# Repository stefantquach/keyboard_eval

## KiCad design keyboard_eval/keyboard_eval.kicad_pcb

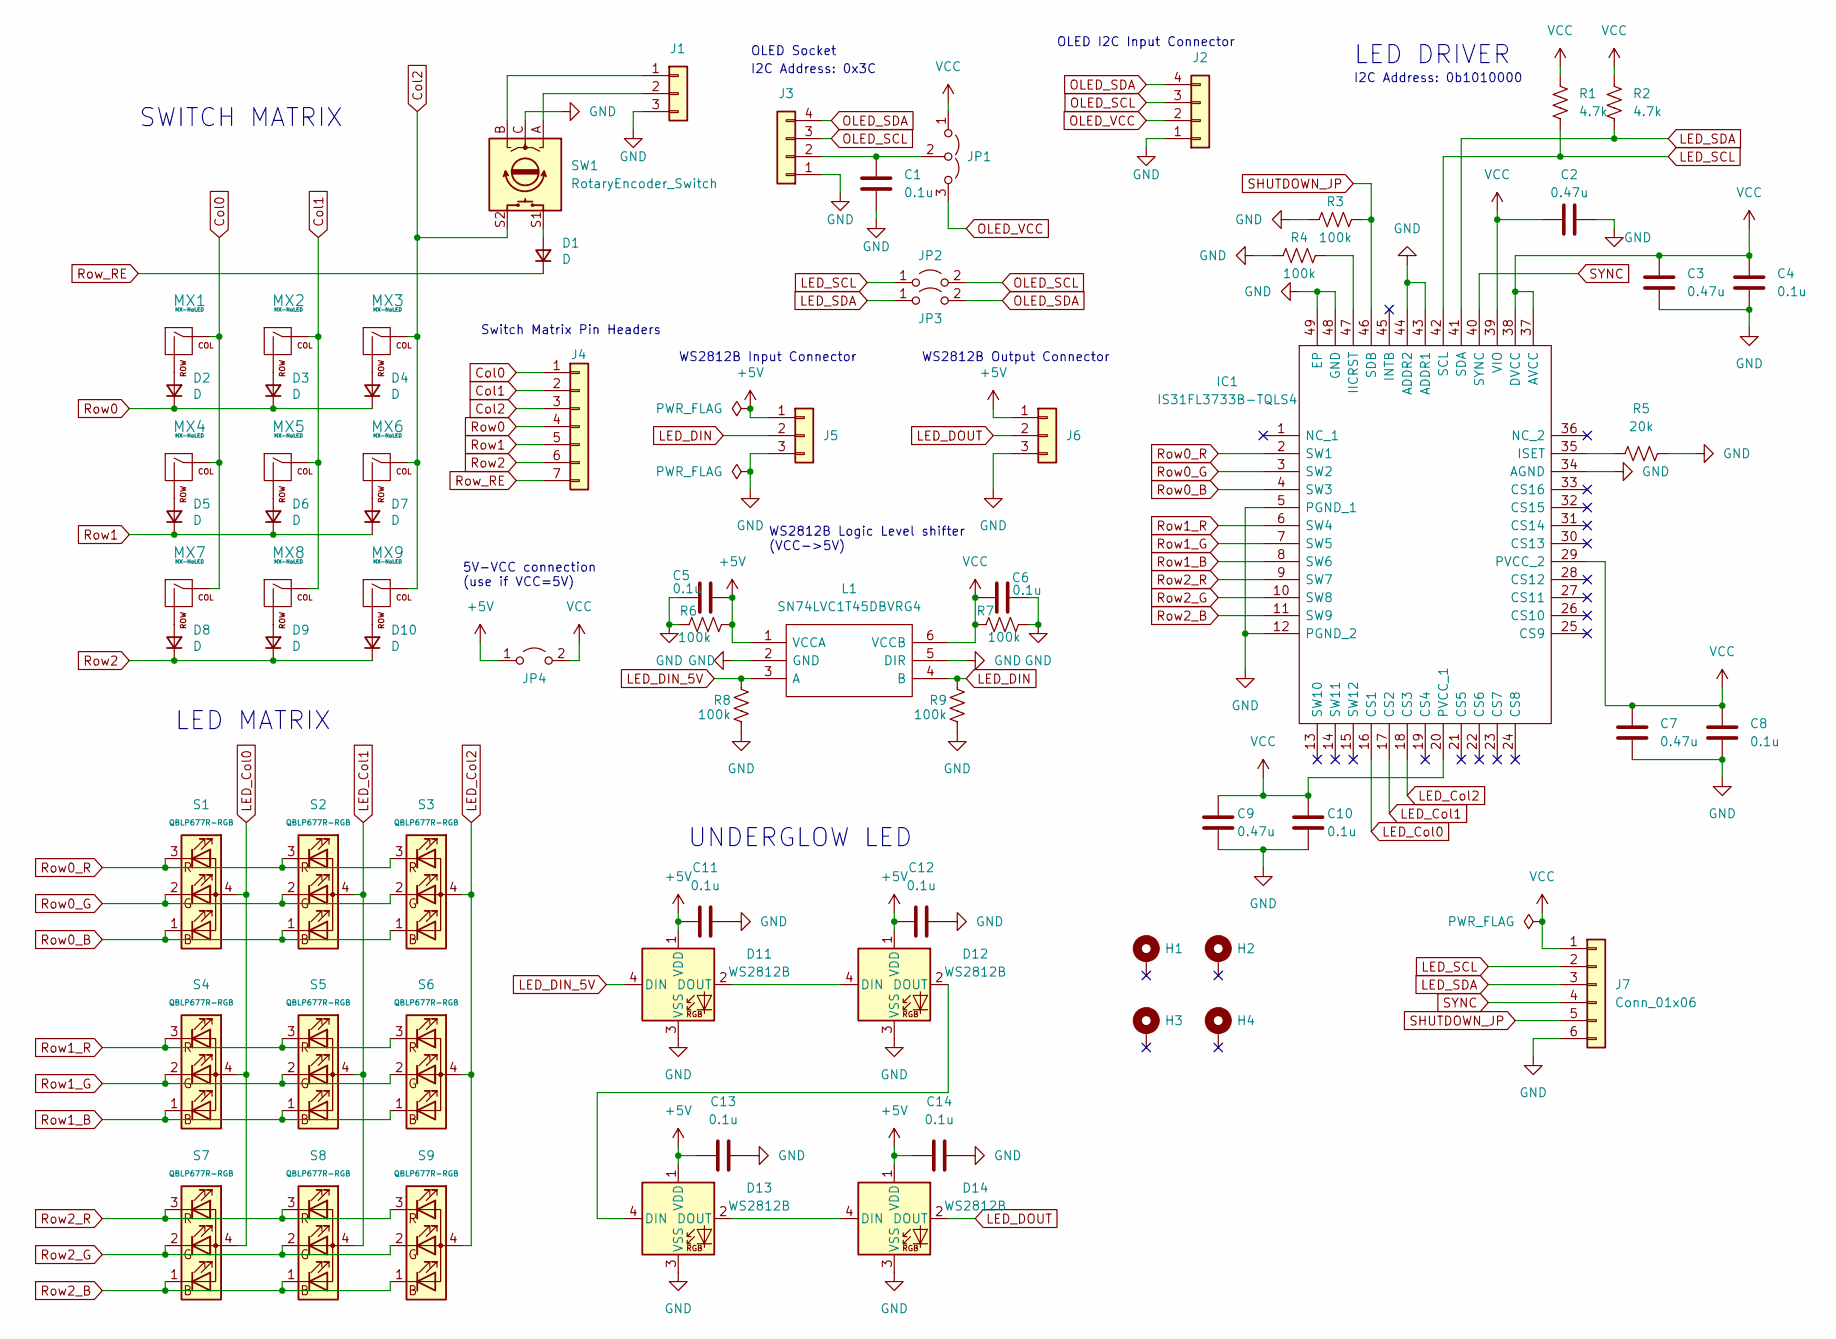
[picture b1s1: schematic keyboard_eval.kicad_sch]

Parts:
C1, C4, C5, C6, C8, C10, C11, C12, C13, C14: 0.1u; C_0603_1608Metric_Pad1.08x0.95mm_HandSolder
C2, C3, C7, C9: 0.47u; C_0603_1608Metric_Pad1.08x0.95mm_HandSolder
D1, D2, D3, D4, D5, D6, D7, D8, D9, D10: D; D_SOD-123-Pretty
D11, D12, D13, D14: WS2812B; LED_WS2812B_PLCC4_5.0x5.0mm_P3.2mm
H1, H2, H3, H4: MountingHole_Pad; MountingHole_2.2mm_M2_DIN965_Pad_TopBottom
IC1: IS31FL3733B-TQLS4; QFP50P900X900X120-49N; Manufacturer_Part_Number IS31FL3733B-TQLS4; Mouser Part Number 870-IS313733B-TQLS4
J1, J5, J6: Conn_01x03; PinHeader_1x03_P2.54mm_Vertical
J2, J3: Conn_01x04; PinHeader_1x04_P2.54mm_Vertical
J4: Conn_01x07; PinHeader_1x07_P2.54mm_Vertical
J7: Conn_01x06; PinHeader_1x06_P2.54mm_Vertical
JP1: Jumper_3_Open; SolderJumper-3_P1.3mm_Open_RoundedPad1.0x1.5mm
JP2, JP3, JP4: Jumper_2_Open; SolderJumper-2_P1.3mm_Open_RoundedPad1.0x1.5mm
L1: SN74LVC1T45DBVRG4; SOT95P280X145-6N; Manufacturer_Part_Number SN74LVC1T45DBVRG4; Mouser Part Number 595-74LVC1T45DBVRG4
MX1, MX2, MX3, MX4, MX5, MX6, MX7, MX8, MX9: MX-NoLED; MX-Hotswap-1U
R1, R2: 4.7k; R_0603_1608Metric_Pad0.98x0.95mm_HandSolder
R3, R4, R6, R7, R8, R9: 100k; R_0603_1608Metric_Pad0.98x0.95mm_HandSolder
R5: 20k; R_0603_1608Metric_Pad0.98x0.95mm_HandSolder
S1, S2, S3, S4, S5, S6, S7, S8, S9: QBLP677R-RGB; QBLP677R-RGB-square_cutout
SW1: RotaryEncoder_Switch; RotaryEncoder_Alps_EC11E-Switch-Vertical-EDIT

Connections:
+5V: C5.2, C11.1, C12.1, C13.1, C14.1, D11.1 (VDD), D12.1 (VDD), D13.1 (VDD), D14.1 (VDD), J5.1, J6.1, JP4.1 (A), L1.1 (VCCA), R6.1
Col0: J4.1, MX1.1 (COL), MX4.1 (COL), MX7.1 (COL)
Col1: J4.2, MX2.1 (COL), MX5.1 (COL), MX8.1 (COL)
Col2: J4.3, MX3.1 (COL), MX6.1 (COL), MX9.1 (COL), SW1.S2
GND: C1.2, C2.2, C3.2, C4.2, C5.1, C6.2, C7.2, C8.2, C9.2, C10.2, C11.2, C12.2, C13.2, C14.2, D11.3 (VSS), D12.3 (VSS), D13.3 (VSS), D14.3 (VSS), IC1.5 (PGND_1), IC1.12 (PGND_2), IC1.34 (AGND), IC1.43 (ADDR1), IC1.44 (ADDR2), IC1.48 (GND), IC1.49 (EP), J1.3, J2.1, J3.1, J5.3, J6.3, J7.6, L1.2 (GND), L1.5 (DIR), R3.1, R4.1, R5.2, R6.2, R7.1, R8.1, R9.1, SW1.C
LED_Col0: IC1.16 (CS1), S1.4 (A), S4.4 (A), S7.4 (A)
LED_Col1: IC1.17 (CS2), S2.4 (A), S5.4 (A), S8.4 (A)
LED_Col2: IC1.18 (CS3), S3.4 (A), S6.4 (A), S9.4 (A)
LED_DIN: J5.2, L1.4 (B), R9.2
LED_DIN_5V: D11.4 (DIN), L1.3 (A), R8.2
LED_DOUT: D14.2 (DOUT), J6.2
LED_SCL: IC1.42 (SCL), J7.2, JP2.1 (A), R1.2
LED_SDA: IC1.41 (SDA), J7.3, JP3.1 (A), R2.2
unnamed: C1.1, J3.2, JP1.2 (C)
unnamed: D1.2 (A), SW1.S1
unnamed: D2.2 (A), MX1.2 (ROW)
unnamed: D3.2 (A), MX2.2 (ROW)
unnamed: D4.2 (A), MX3.2 (ROW)
unnamed: D5.2 (A), MX4.2 (ROW)
unnamed: D6.2 (A), MX5.2 (ROW)
unnamed: D7.2 (A), MX6.2 (ROW)
unnamed: D8.2 (A), MX7.2 (ROW)
unnamed: D9.2 (A), MX8.2 (ROW)
unnamed: D10.2 (A), MX9.2 (ROW)
unnamed: D11.2 (DOUT), D12.4 (DIN)
unnamed: D12.2 (DOUT), D13.4 (DIN)
unnamed: D13.2 (DOUT), D14.4 (DIN)
unnamed: IC1.35 (ISET), R5.1
unnamed: IC1.47 (IICRST), R4.2
unnamed: J1.1, SW1.B
unnamed: J1.2, SW1.A
OLED_SCL: J2.3, J3.3, JP2.2 (B)
OLED_SDA: J2.4, J3.4, JP3.2 (B)
OLED_VCC: J2.2, JP1.3 (B)
Row0: D2.1 (K), D3.1 (K), D4.1 (K), J4.4
Row0_B: IC1.4 (SW3), S1.1 (BK), S2.1 (BK), S3.1 (BK)
Row0_G: IC1.3 (SW2), S1.2 (GK), S2.2 (GK), S3.2 (GK)
Row0_R: IC1.2 (SW1), S1.3 (RK), S2.3 (RK), S3.3 (RK)
Row1: D5.1 (K), D6.1 (K), D7.1 (K), J4.5
Row1_B: IC1.8 (SW6), S4.1 (BK), S5.1 (BK), S6.1 (BK)
Row1_G: IC1.7 (SW5), S4.2 (GK), S5.2 (GK), S6.2 (GK)
Row1_R: IC1.6 (SW4), S4.3 (RK), S5.3 (RK), S6.3 (RK)
Row2: D8.1 (K), D9.1 (K), D10.1 (K), J4.6
Row2_B: IC1.11 (SW9), S7.1 (BK), S8.1 (BK), S9.1 (BK)
Row2_G: IC1.10 (SW8), S7.2 (GK), S8.2 (GK), S9.2 (GK)
Row2_R: IC1.9 (SW7), S7.3 (RK), S8.3 (RK), S9.3 (RK)
Row_RE: D1.1 (K), J4.7
SHUTDOWN_JP: IC1.46 (SDB), J7.5, R3.2
SYNC: IC1.40 (SYNC), J7.4
VCC: C2.1, C3.1, C4.1, C6.1, C7.1, C8.1, C9.1, C10.1, IC1.20 (PVCC_1), IC1.29 (PVCC_2), IC1.37 (AVCC), IC1.38 (DVCC), IC1.39 (VIO), J7.1, JP1.1 (A), JP4.2 (B), L1.6 (VCCB), R1.1, R2.1, R7.2

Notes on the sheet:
OLED I2C Input Connector
I2C Address: 0x3C
UNDERGLOW LED
LED DRIVER
5V-VCC connection (use if VCC=5V)
WS2812B Output Connector
I2C Address: 0b1010000
WS2812B Logic Level shifter (VCC->5V)
SWITCH MATRIX
WS2812B Input Connector
OLED Socket
LED MATRIX
Switch Matrix Pin Headers

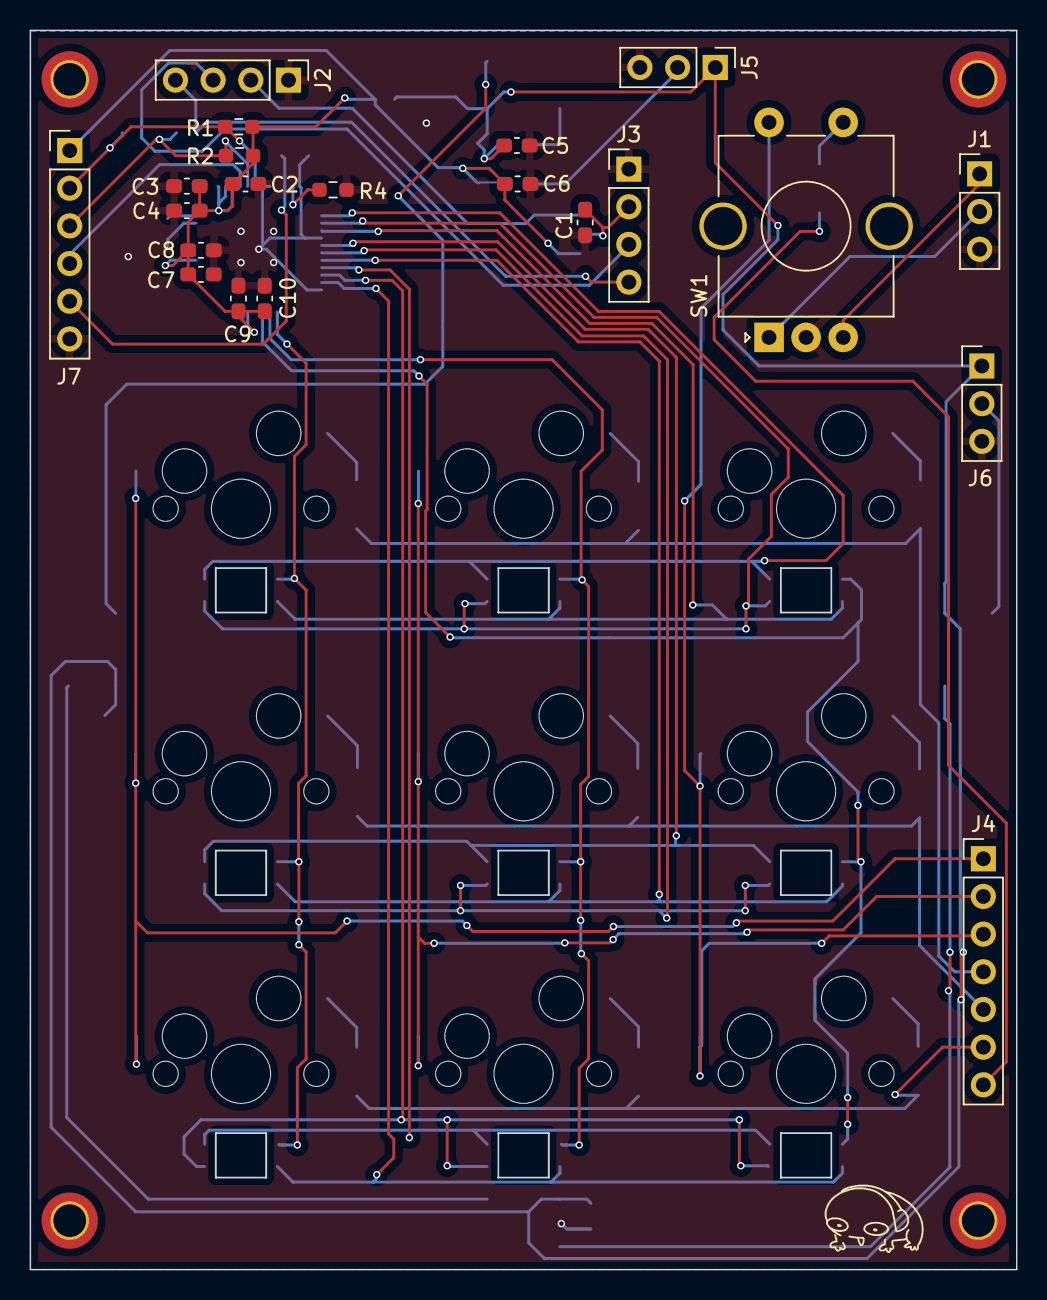
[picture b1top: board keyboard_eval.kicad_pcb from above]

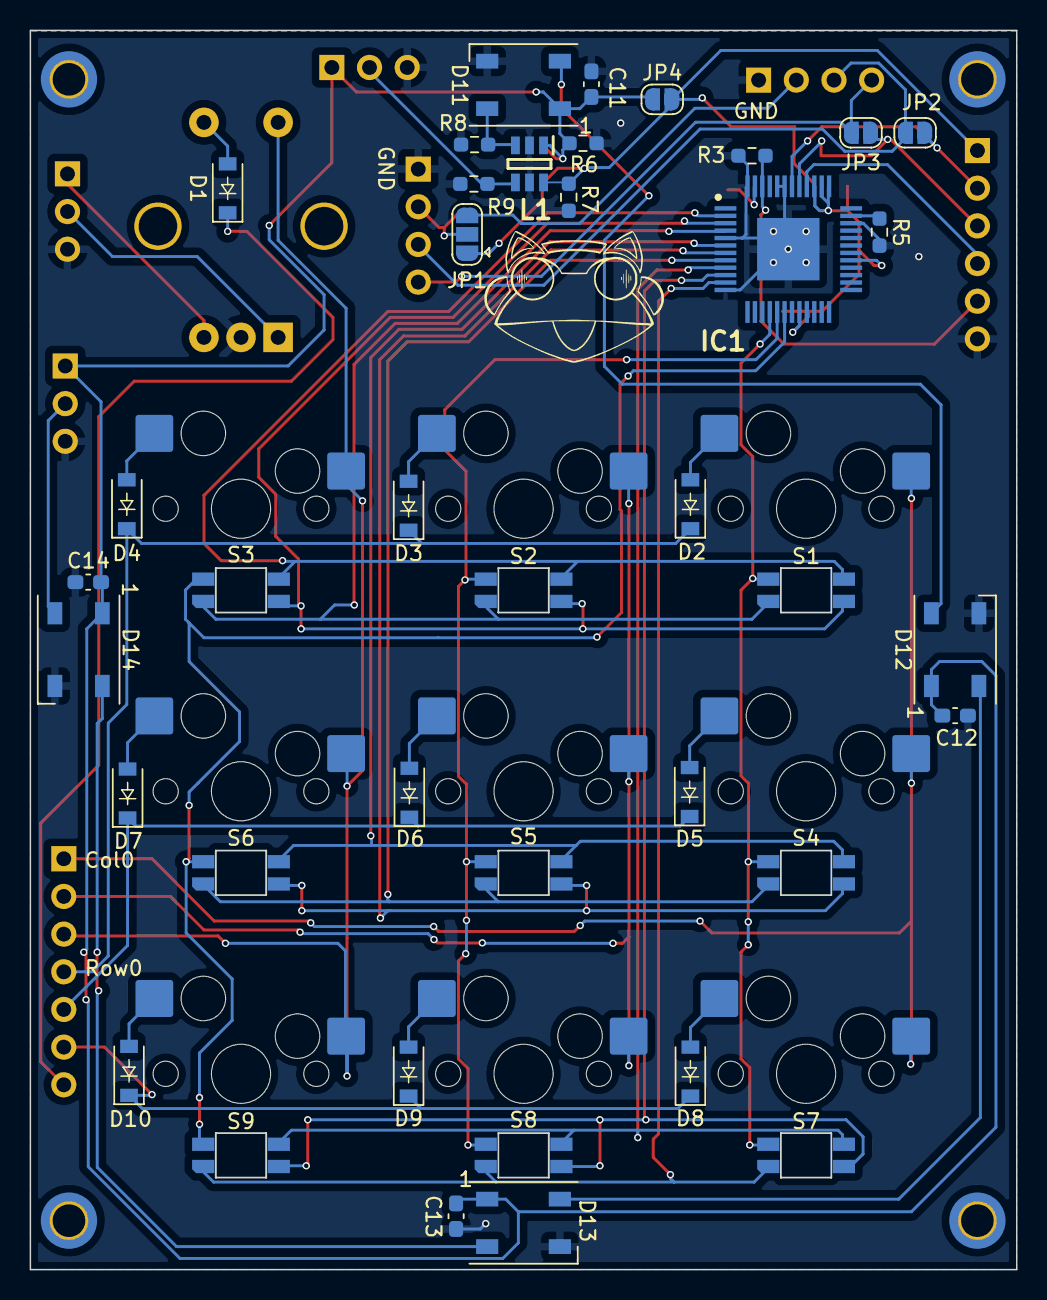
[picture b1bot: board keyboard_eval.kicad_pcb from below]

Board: 2 copper layers, 66.5 x 83.5 mm, 73 parts (39 on the bottom side), 50 nets.

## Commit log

2022-12-22 Initial commit of schematic and WIP layout
2022-12-23 WIP layout
2022-12-24 Finished initial layout
2022-12-25 Fixing RGB LED footprint. Fixing missing bits of copper fill
2023-01-01 removing backups folder
2023-01-01 Adding gerbers and pdf schematic
2023-01-15 Adding firmware. WIP
2023-01-22 Fixing schematics and firmware
2023-01-22 Updating pdf sch and gerbers to fix layout bugs
